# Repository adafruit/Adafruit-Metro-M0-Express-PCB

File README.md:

## Adafruit METRO M0 Express - designed for CircuitPython - ATSAMD21G18 PCB

<a href="http://www.adafruit.com/products/3505"><br/>
Click here to purchase one from the Adafruit shop</a>

PCB files for the Adafruit METRO M0 Express - designed for CircuitPython - ATSAMD21G18. Format is EagleCAD schematic and board layout
* https://www.adafruit.com/product/3505

### Description

Metro is our series of microcontroller boards for use with the Arduino IDE. This new **Metro M0 Express** board looks a whole lot like our [original Metro 328](https://www.adafruit.com/product/2488), but with a huge upgrade. Instead of the ATmega328, this Metro features a ATSAMD21G18 chip, an ARM Cortex M0+. It's our first Metro that is designed for use with CircuitPython! CircuitPython is our beginner-oriented flavor of MicroPython - and as the name hints at, its a small but full-featured version of the popular Python programming language specifically for use with circuitry and electronics.

Not only can you use CircuitPython, but the Metro M0 is also usable in the Arduino IDE.

At the Metro M0's heart is an ATSAMD21G18 ARM Cortex M0 processor, clocked at 48 MHz and at 3.3V logic, the same one used in the new [Arduino Zero](https://www.adafruit.com/products/2843). This chip has a whopping 256K of FLASH (8x more than the Atmega328) and 32K of RAM (16x as much)! This chip comes with built in USB so it has USB-to-Serial program & debug capability built in with no need for an FTDI-like chip.

 * **Power the METRO** with 7-9V polarity protected DC or the micro USB connector to any 5V USB source. The 2.1mm DC jack has an on/off switch next to it so you can turn off your setup easily. The METRO will automagically switch between USB and DC.
 * **METRO has 25 GPIO pins**, 12 of which are analog in, and one of which is a true analog out. There's a hardware SPI port, hardware I2C port and hardware UART. Logic level is 3.3V
 * **Native USB**, there's no need for a hardware USB to Serial converter as the Metro M0 has built in USB support. When used to act like a serial device, the USB interface can be used by any computer to listen/send data to the METRO, and can also be used to launch and update code via the bootloader. It can also act like a keyboard, mouse or MIDI device as well.
 * **Four indicator LEDs and one NeoPixel**, on the front edge of the PCB, for easy debugging. One green power LED, two RX/TX LEDs for data being sent over USB, and a red LED connected. Next to the reset button there is an RGB NeoPixel that can be used for any purpose.
 * **2 MB SPI Flash** storage chip is included on board. You can use the SPI Flash storage like a very tiny hard drive. When used in Circuit Python, the 2 MB flash acts as storage for all your scripts, libraries and files. When used in Arduino, you can read/write files to it, like a little datalogger or SD card, and then with our helper program, access the files over USB.
 * **Easy reprogramming**, comes pre-loaded with the [UF2 bootloader](https://learn.adafruit.com/adafruit-metro-m0-express-designed-for-circuitpython/uf2-bootloader), which looks like a USB storage key. Simply drag firmware on to program, no special tools or drivers needed! It can be used to load up CircuitPython, PXT/MakeCode or Arduino IDE (it is bossa-compatible)
Comes fully assembled with headers, tested, and with the UF2 bootloader loaded on. We also include 4 rubber bumpers to keep it from slipping off your desk. No soldering required to use, plug and play!

Good news, CircuitPython now comes preloaded!

[Check out our full guide for pinouts, schematics, drivers, instructions, Fritzing object, and more!](https://learn.adafruit.com/adafruit-metro-m0-express-designed-for-circuitpython)

### License

Adafruit invests time and resources providing this open source design, please support Adafruit and open-source hardware by purchasing products from [Adafruit](https://www.adafruit.com)!

Designed by Limor Fried/Ladyada for Adafruit Industries.

Creative Commons Attribution/Share-Alike, all text above must be included in any redistribution. See license.txt for additional details.

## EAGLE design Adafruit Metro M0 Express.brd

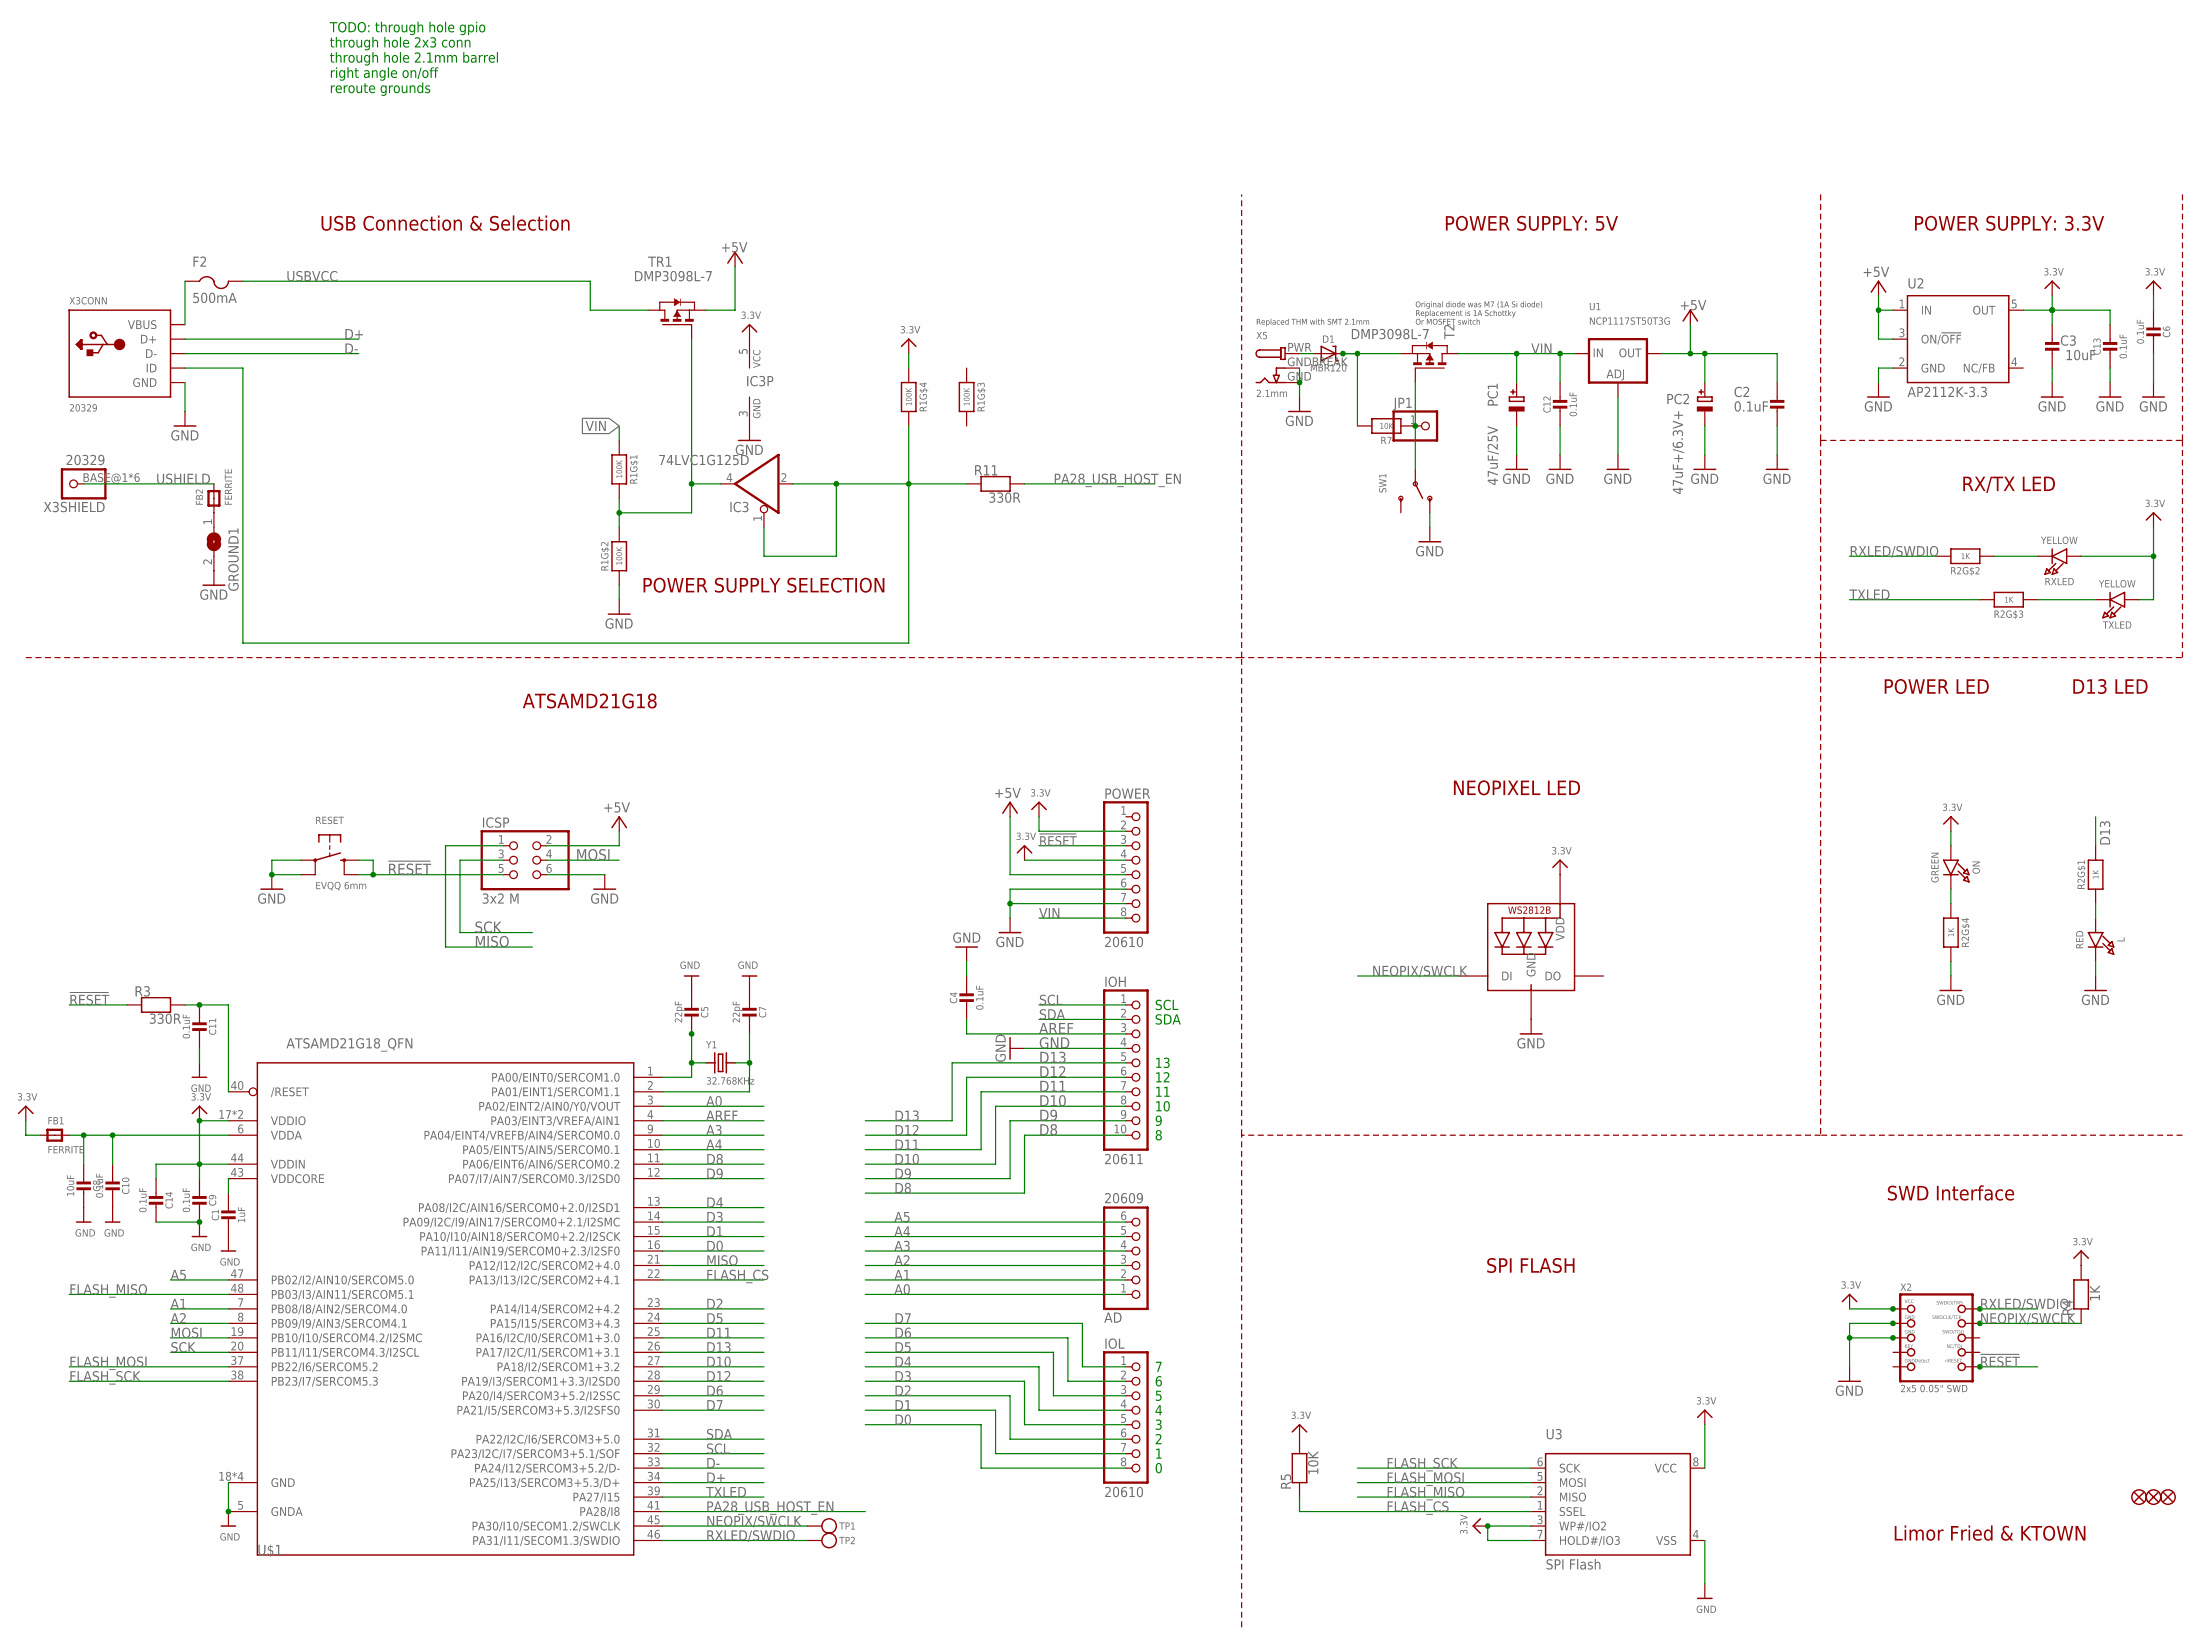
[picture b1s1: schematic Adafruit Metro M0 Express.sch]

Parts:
AD: 20609; 1X06_OVALWAVE
C1: 1uF; 0805-NO
C2, C4, C6, C9, C10, C11, C12, C13, C14: 0.1uF; 0805-NO
C3, C8: 10uF; 0805-NO
C5, C7: 22pF; 0805-NO
D1: MBR120; SOD-123
F2: 500mA; R1206
FB1, FB2: FERRITE; 0805-NO
FD1, FD2, FD3: FIDUCIAL_1MM
GROUND1: SJ
IC3: 74LVC1G125D; SOT23-5
ICSP: 3x2 M; 2X03_ROUND_70MIL
IOH: 20611; 1X10_OVALWAVE
IOL: 20610; 1X08_OVALWAVE
JP1: HEADER-1X1ROUND; 1X01_ROUND
L: RED; CHIPLED_0805_NOOUTLINE
LED1: WS2812B3535; LED3535
ON: GREEN; CHIPLED_0805_NOOUTLINE
PC1: 47uF/25V; PANASONIC_D
PC2: 47uF+/6.3V+; PANASONIC_D
POWER: 20610; 1X08_OVALWAVE
R1: 100K; RESPACK_4X0603
R2: 1K; RESPACK_4X0603
R3, R11: 330R; 0805-NO
R4: 1K; 0805-NO
R5, R7: 10K; 0805-NO
RESET: EVQQ 6mm; EVQ-Q2
RXLED: YELLOW; CHIPLED_0805_NOOUTLINE
SW1: SWITCH_SPDT; SPDT_SMT_SSSS811101
T2: DMP3098L-7; SOT-23
TP1, TP2: TESTPOINTROUND1.5MM; TESTPOINT_ROUND_1.5MM
TR1: DMP3098L-7; SOT-23
TXLED: YELLOW; CHIPLED_0805_NOOUTLINE
U1: NCP1117ST50T3G; SOT223-R
U2: AP2112K-3.3; SOT23-DBV
U3: SPI Flash; SOIC8_208MIL
U$1: ATSAMD21G18_QFN; TQFN48_7MM
X2: 2x5 0.05" SWD; 2X05_1.27MM_BOX_POSTS
X3: 20329; 4UCONN_20329_V2
X5: 2.1mm; DCJACK_2MM_PTH
Y1: 32.768KHz; CRYSTAL_8X3.8

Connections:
3.3V: C3.2, C6.2, C9.2, C13.1, C14.2, FB1.1, IC3.5 (VCC), LED1.2 (VDD), ON.A, POWER.2, POWER.4, R1.4 (1), R4.2, R5.2, RXLED.A, TXLED.A, U2.5 (OUT), U3.3 (WP#/IO2), U3.7 (HOLD#/IO3), U3.8 (VCC), U$1.17 (VDDIO), U$1.36 (VDDIO), U$1.44 (VDDIN), X2.1 (VCC)
!RESET: ICSP.5, POWER.3, R3.1, RESET.B (S), RESET.B' (S1), X2.10 (NRESET)
+5V: C2.2, ICSP.2, PC2.+, POWER.5, TR1.2 (S), U1.2 (OUT), U1.4 (OUT), U2.1 (IN), U2.3 (ON/!OFF)
A0: AD.1, U$1.3 (PA02/EINT2/AIN0/Y0/VOUT)
A1: AD.2, U$1.7 (PB08/I8/AIN2/SERCOM4.0)
A2: AD.3, U$1.8 (PB09/I9/AIN3/SERCOM4.1)
A3: AD.4, U$1.9 (PA04/EINT4/VREFB/AIN4/SERCOM0.0)
A4: AD.5, U$1.10 (PA05/EINT5/AIN5/SERCOM0.1)
A5: AD.6, U$1.47 (PB02/I2/AIN10/SERCOM5.0)
AREF: C4.2, IOH.3, U$1.4 (PA03/EINT3/VREFA/AIN1)
AVCC: C8.2, C10.2, FB1.2, U$1.6 (VDDA)
D0: IOL.8, U$1.16 (PA11/I11/AIN19/SERCOM0+2.3/I2SF0)
D1: IOL.7, U$1.15 (PA10/I10/AIN18/SERCOM0+2.2/I2SCK)
D2: IOL.6, U$1.23 (PA14/I14/SERCOM2+4.2)
D3: IOL.5, U$1.14 (PA09/I2C/I9/AIN17/SERCOM0+2.1/I2SMC)
D4: IOL.4, U$1.13 (PA08/I2C/AIN16/SERCOM0+2.0/I2SD1)
D5: IOL.3, U$1.24 (PA15/I15/SERCOM3+4.3)
D6: IOL.2, U$1.29 (PA20/I4/SERCOM3+5.2/I2SSC)
D7: IOL.1, U$1.30 (PA21/I5/SERCOM3+5.3/I2SFS0)
D8: IOH.10, U$1.11 (PA06/EINT6/AIN6/SERCOM0.2)
D9: IOH.9, U$1.12 (PA07/I7/AIN7/SERCOM0.3/I2SD0)
D10: IOH.8, U$1.27 (PA18/I2/SERCOM1+3.2)
D11: IOH.7, U$1.25 (PA16/I2C/I0/SERCOM1+3.0)
D12: IOH.6, U$1.28 (PA19/I3/SERCOM1+3.3/I2SD0)
D13: IOH.5, R2.8 (2), U$1.26 (PA17/I2C/I1/SERCOM1+3.1)
D+: U$1.34 (PA25/I13/SERCOM3+5.3/D+), X3.D+
D-: U$1.33 (PA24/I12/SERCOM3+5.2/D-), X3.D-
FLASH_CS: R5.1, U3.1 (SSEL), U$1.22 (PA13/I13/I2C/SERCOM2+4.1)
FLASH_MISO: U3.2 (MISO), U$1.48 (PB03/I3/AIN11/SERCOM5.1)
FLASH_MOSI: U3.5 (MOSI), U$1.37 (PB22/I6/SERCOM5.2)
FLASH_SCK: U3.6 (SCK), U$1.38 (PB23/I7/SERCOM5.3)
GND: C1.2, C2.1, C3.1, C4.1, C5.2, C6.1, C7.2, C8.1, C9.1, C10.1, C11.1, C12.2, C13.2, C14.1, GROUND1.2, IC3.3 (GND), ICSP.6, IOH.4, L.C, LED1.4 (GND), PC1.-, PC2.-, POWER.6, POWER.7, R1.2 (1), R2.5 (2), RESET.A, RESET.A' (P1), SW1.A (O), U1.1 (ADJ), U2.2 (GND), U3.4 (VSS), U$1.5 (GNDA), U$1.18 (GND), U$1.35 (GND), U$1.42 (GND), U$1.THERMAL (GND), X2.3 (GND), X2.5 (GND), X3.GND, X5.GND, X5.GNDBREAK
MISO: ICSP.1, U$1.21 (PA12/I12/I2C/SERCOM2+4.0)
MOSI: ICSP.4, U$1.19 (PB10/I10/SERCOM4.2/I2SMC)
unnamed: L.A, R2.1
unnamed: FB2.1, GROUND1.1
unnamed: ON.C, R2.4 (1)
unnamed: C5.1, U$1.1 (PA00/EINT0/SERCOM1.0), Y1.P$1 (1)
unnamed: R2.2 (1), RXLED.C
unnamed: C7.1, U$1.2 (PA01/EINT1/SERCOM1.1), Y1.P$4 (2)
unnamed: R2.3 (1), TXLED.C
unnamed: C11.2, R3.2, U$1.40 (/RESET)
unnamed: D1.A, X5.PWR
unnamed: IC3.1 (OE), IC3.2 (I), R1.5 (2), R11.1, X3.ID
unnamed: IC3.4 (O), R1.7 (2), R1.8 (2), TR1.3 (G)
unnamed: JP1.1, R7.1, SW1.B, T2.3 (G)
unnamed: D1.C, R7.2, T2.2 (S)
NEOPIX/SWCLK: LED1.1 (DI), R4.1, TP1.P$1, U$1.45 (PA30/I10/SECOM1.2/SWCLK), X2.4 (SWDCLK)
PA28_USB_HOST_EN: R11.2, U$1.41 (PA28/I8)
RXLED/SWDIO: R2.7 (2), TP2.P$1, U$1.46 (PA31/I11/SECOM1.3/SWDIO), X2.2 (SWDIO)
SCK: ICSP.3, U$1.20 (PB11/I11/SERCOM4.3/I2SCL)
SCL: IOH.1, U$1.32 (PA23/I2C/I7/SERCOM3+5.1/SOF)
SDA: IOH.2, U$1.31 (PA22/I2C/I6/SERCOM3+5.0)
TXLED: R2.6 (2), U$1.39 (PA27/I15)
USBVCC: F2.2, TR1.1 (D)
USHIELD: FB2.2, X3.BASE@1 (1), X3.BASE@2 (1), X3.SPRT@1 (1), X3.SPRT@2 (1), X3.SPRT@3 (1), X3.SPRT@4 (1)
VBUS: F2.1, X3.VBUS
VDDCORE: C1.1, U$1.43 (VDDCORE)
VIN: C12.1, PC1.+, POWER.8, R1.1, T2.1 (D), U1.3 (IN)

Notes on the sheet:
SDA
SCL
Limor Fried & KTOWN
Original diode was M7 (1A Si diode) Replacement is 1A Schottky Or MOSFET switch
Replaced THM with SMT 2.1mm
POWER SUPPLY: 5V
USB Connection & Selection
POWER SUPPLY: 3.3V
POWER LED
ATSAMD21G18
POWER SUPPLY SELECTION
D13 LED
RX/TX LED
NEOPIXEL LED
SPI FLASH
SWD Interface
TODO: through hole gpio through hole 2x3 conn through hole 2.1mm barrel right angle on/off reroute grounds

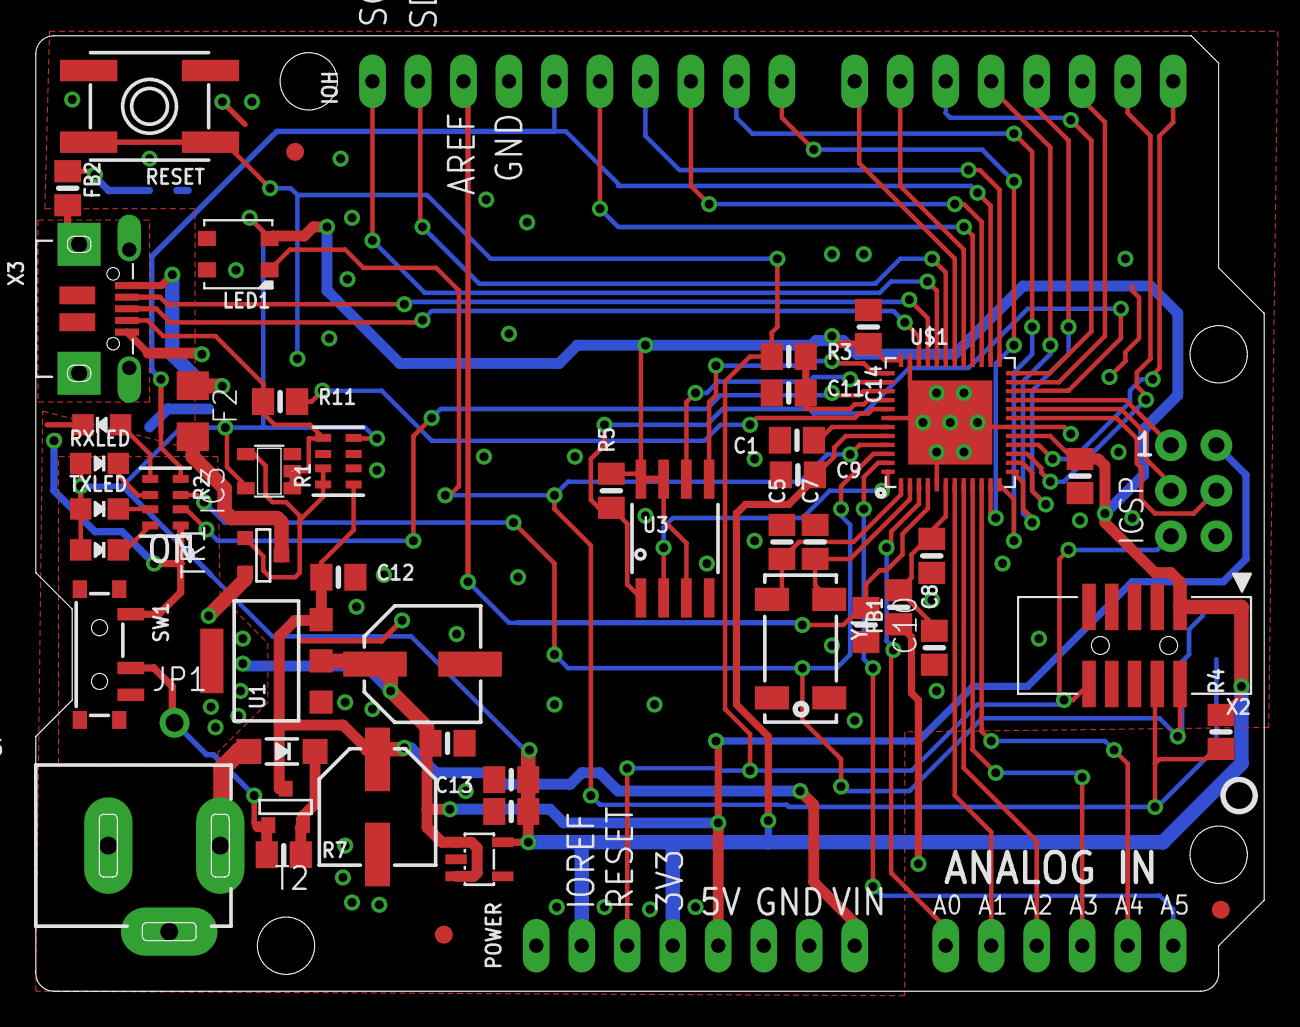
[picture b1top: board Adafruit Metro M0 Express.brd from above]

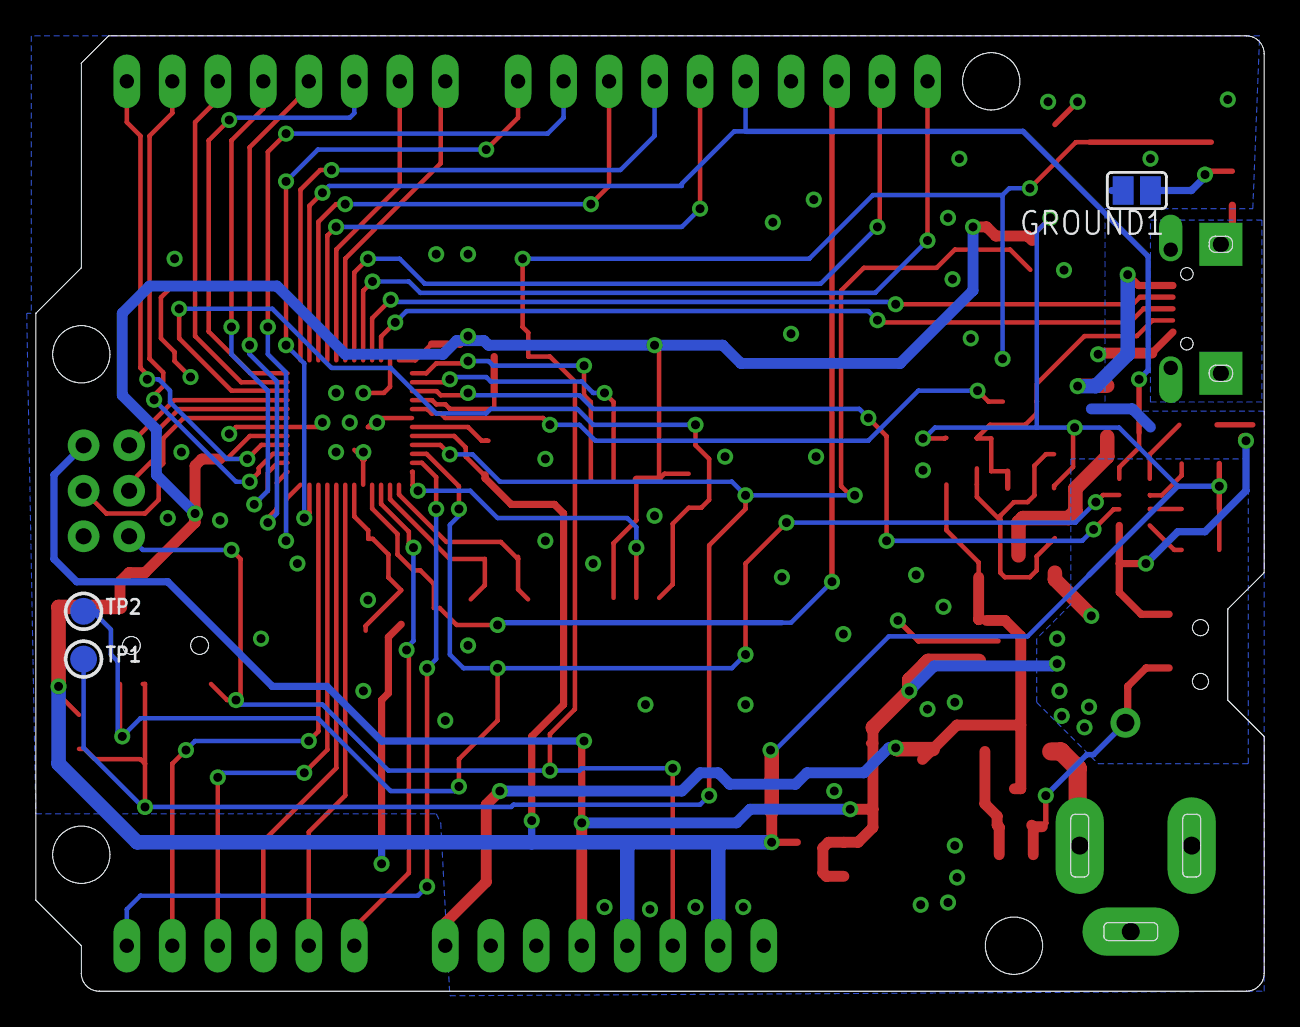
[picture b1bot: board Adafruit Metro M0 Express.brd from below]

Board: 2 copper layers, 68.6 x 53.3 mm, 60 parts (4 on the bottom side), 59 nets.

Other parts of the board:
U$11: METRO_M0_BACK
U$14: PCBFEAT-REV-040
U$30: METRO_M0_FRONT

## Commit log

2017-06-14 initty!@
2019-02-19 Deleting file to update.
2019-02-19 Updating board files.
2019-07-17 updated to use cookiecutter for pcb repos
2022-04-19 Added PrettyPins

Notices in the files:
parts and their libraries:
microbuilder: This work is placed in the public domain, and may be freely used for commercial and non-commercial work with the following conditions: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
